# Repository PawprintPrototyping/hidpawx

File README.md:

# HIDPawx
NFC based badging system for equipment lockout

(not HID Prox Compatible)

Closely based on BeepBeep by MemberMatters, but tailored around NFC and 
designed primarily for equipment lockout.

## Maintainers
- Kay Barkbark

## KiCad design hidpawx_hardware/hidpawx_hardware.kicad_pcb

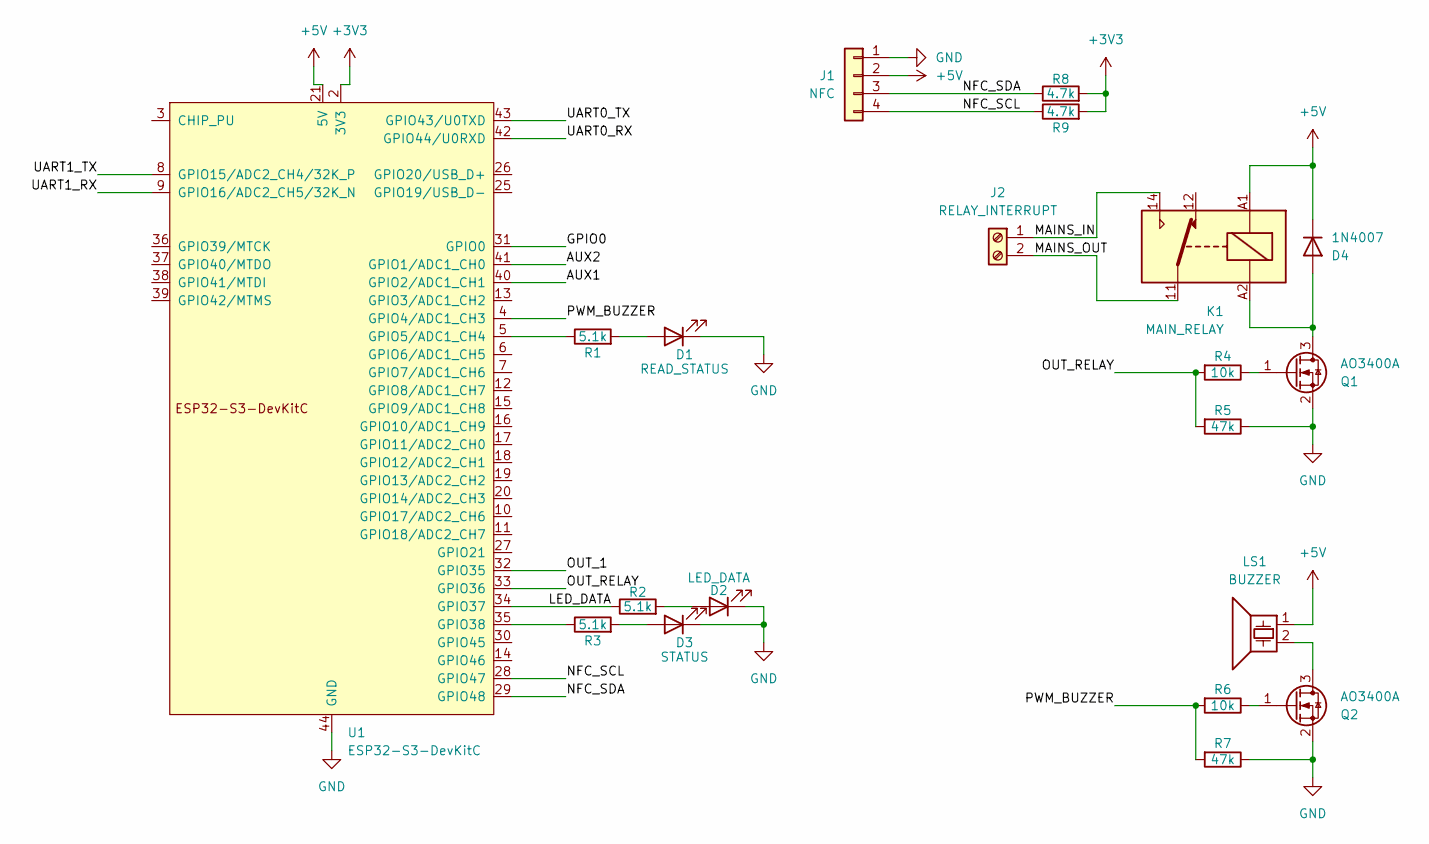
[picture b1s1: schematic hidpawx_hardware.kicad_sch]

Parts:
D1: READ_STATUS; LED_1210_3225Metric
D2: LED_DATA; LED_1210_3225Metric
D3: STATUS; LED_1210_3225Metric
D4: 1N4007; D_DO-41_SOD81_P10.16mm_Horizontal
J1: NFC; PinHeader_1x04_P2.54mm_Vertical
J2: RELAY_INTERRUPT; CONN_1759017_PXC
K1: MAIN_RELAY; Relay_SPDT_Hongfa_JQC-3FF_0XX-1Z
LS1: BUZZER; Buzzer_12x9.5RM7.6
Q1, Q2: AO3400A; SOT-23
R1, R2, R3: 5.1k; R_0805_2012Metric_Pad1.20x1.40mm_HandSolder
R4, R6: 10k; R_0805_2012Metric_Pad1.20x1.40mm_HandSolder
R5, R7: 47k; R_0805_2012Metric_Pad1.20x1.40mm_HandSolder
R8, R9: 4.7k; R_0805_2012Metric_Pad1.20x1.40mm_HandSolder
U1: ESP32-S3-DevKitC

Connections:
+3V3: R8.2, R9.2, U1.1 (3V3), U1.2 (3V3)
+5V: D4.1 (K), J1.2, K1.A1, LS1.1, U1.21 (5V)
/AUX1: U1.40 (GPIO2/ADC1_CH1)
/AUX2: U1.41 (GPIO1/ADC1_CH0)
/GPIO0: U1.31 (GPIO0)
/LED_DATA: R2.1, U1.34 (GPIO37)
/MAINS_IN: J2.1, K1.14
/MAINS_OUT: J2.2, K1.11
/NFC_SCL: J1.4, R9.1, U1.28 (GPIO47)
/NFC_SDA: J1.3, R8.1, U1.29 (GPIO48)
/OUT_1: U1.32 (GPIO35)
/OUT_RELAY: R4.2, R5.2, U1.33 (GPIO36)
/PWM_BUZZER: R6.2, R7.2, U1.4 (GPIO4/ADC1_CH3)
/UART0_RX: U1.42 (GPIO44/U0RXD)
/UART0_TX: U1.43 (GPIO43/U0TXD)
/UART1_RX: U1.9 (GPIO16/ADC2_CH5/32K_N)
/UART1_TX: U1.8 (GPIO15/ADC2_CH4/32K_P)
GND: D1.1 (K), D2.1 (K), D3.1 (K), J1.1, Q1.2 (S), Q2.2 (S), R5.1, R7.1, U1.22 (GND), U1.23 (GND), U1.24 (GND), U1.44 (GND)
unnamed: D1.2 (A), R1.2
unnamed: D2.2 (A), R2.2
unnamed: D3.2 (A), R3.2
unnamed: D4.2 (A), K1.A2, Q1.3 (D)
unnamed: Q1.1 (G), R4.1
unnamed: LS1.2, Q2.3 (D)
unnamed: Q2.1 (G), R6.1
unnamed: R1.1, U1.5 (GPIO5/ADC1_CH4)
unnamed: R3.1, U1.35 (GPIO38)

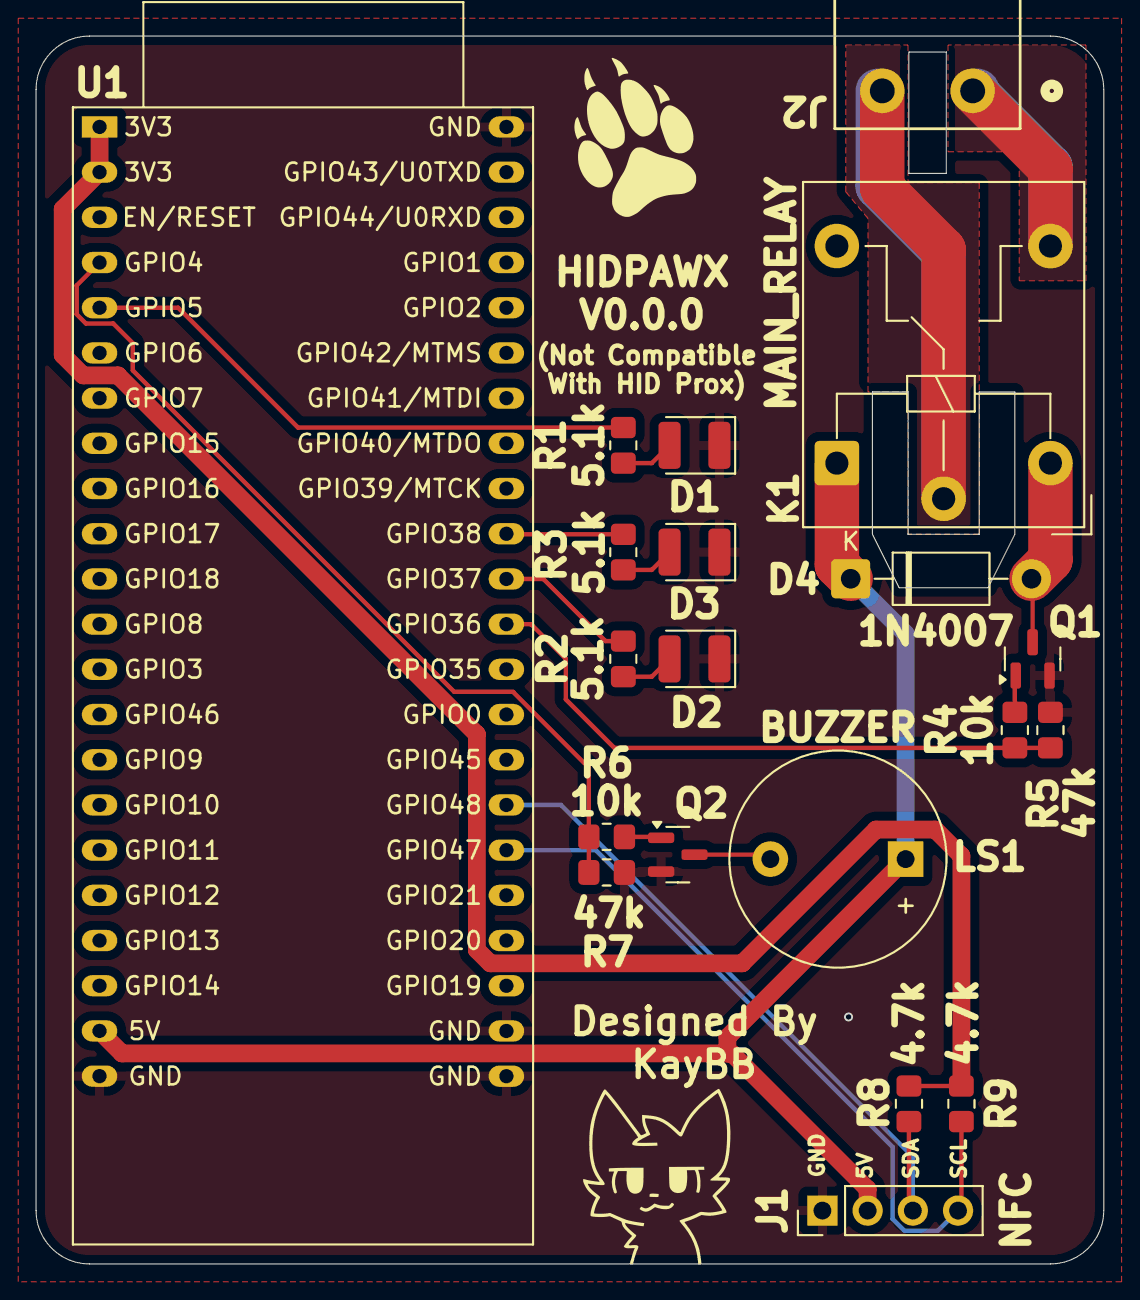
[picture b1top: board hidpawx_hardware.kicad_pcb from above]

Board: 2 copper layers, 60.0 x 69.0 mm, 20 parts (0 on the bottom side), 19 nets.

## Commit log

2025-09-24 first
2025-09-24 added readme
2026-02-02 starting back up on this, need to learn how websockets work
2026-02-03 Experimenting with websockets
